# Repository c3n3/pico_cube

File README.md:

# pico_cube
A LED cube from a pico

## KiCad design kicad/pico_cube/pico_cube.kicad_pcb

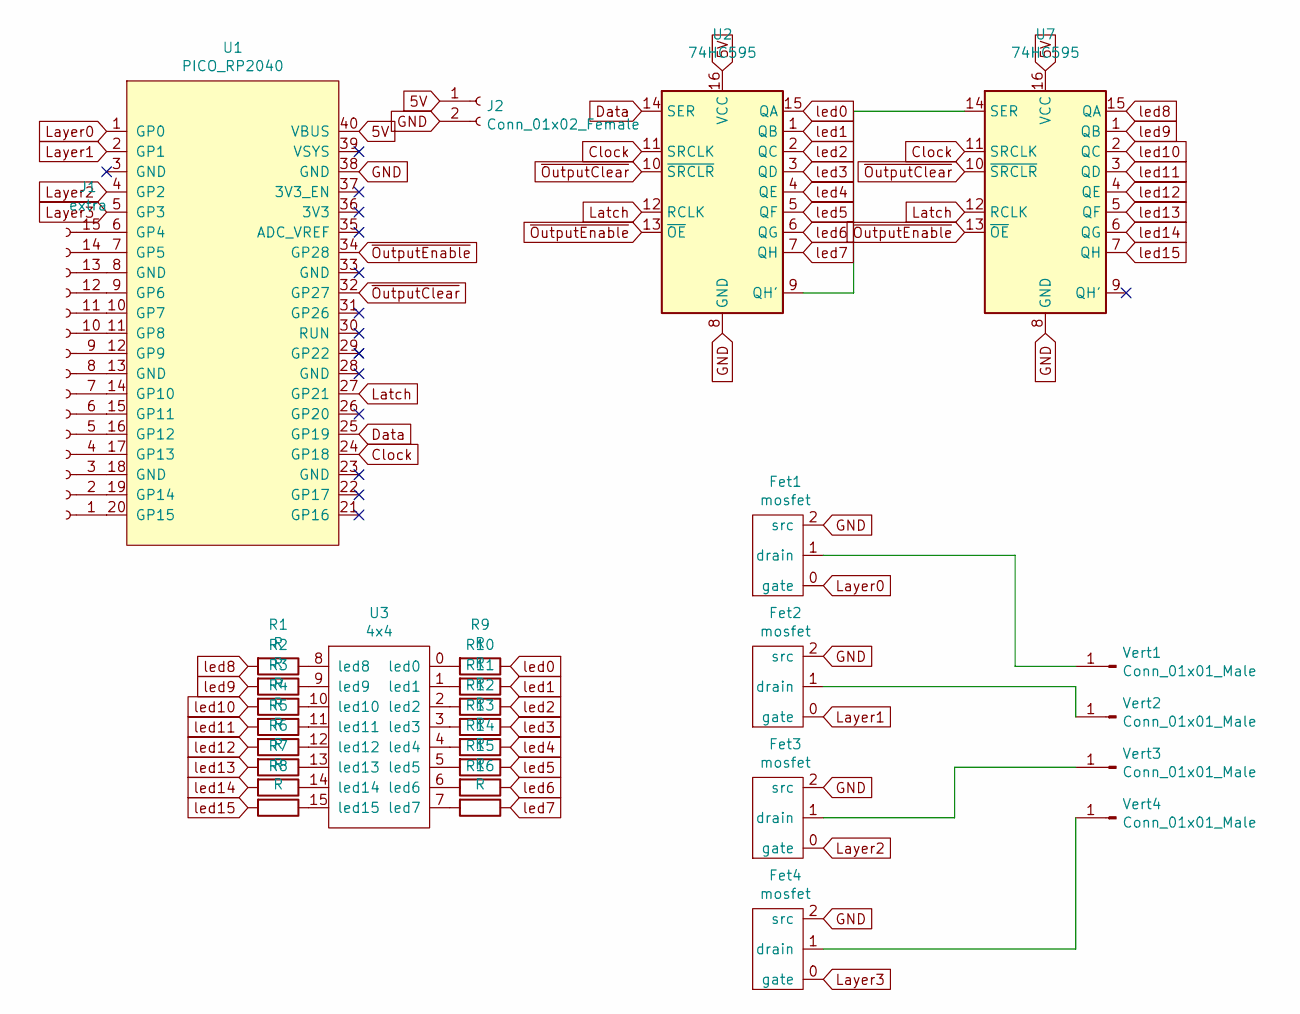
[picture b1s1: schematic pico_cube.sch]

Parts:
Fet1, Fet2, Fet3, Fet4: mosfet
J1: extra; PinHeader_1x15_P2.54mm_Vertical
J2: Conn_01x02_Female; PinHeader_1x02_P2.54mm_Vertical
R1, R2, R3, R4, R5, R6, R7, R8, R9, R10, R11, R12, R13, R14, R15, R16: R; R_Axial_DIN0204_L3.6mm_D1.6mm_P7.62mm_Horizontal
U1: PICO_RP2040; pico
U2, U7: 74HC595; SN74HC595N
U3: 4x4
Vert1, Vert2, Vert3, Vert4: Conn_01x01_Male; pin

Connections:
5V: J2.1, U1.40 (VBUS), U2.16 (VCC), U7.16 (VCC)
Clock: U1.24 (GP18), U2.11 (SRCLK), U7.11 (SRCLK)
Data: U1.25 (GP19), U2.14 (SER)
GND: Fet1.2 (src), Fet2.2 (src), Fet3.2 (src), Fet4.2 (src), J2.2, U1.38 (GND), U2.8 (GND), U7.8 (GND)
Latch: U1.27 (GP21), U2.12 (RCLK), U7.12 (RCLK)
Layer0: Fet1.0 (gate), U1.1 (GP0)
Layer1: Fet2.0 (gate), U1.2 (GP1)
Layer2: Fet3.0 (gate), U1.4 (GP2)
Layer3: Fet4.0 (gate), U1.5 (GP3)
unnamed: Fet1.1 (drain), Vert1.1
unnamed: Fet2.1 (drain), Vert2.1
unnamed: Fet3.1 (drain), Vert3.1
unnamed: Fet4.1 (drain), Vert4.1
unnamed: J1.1, U1.20 (GP15)
unnamed: J1.2, U1.19 (GP14)
unnamed: J1.3, U1.18 (GND)
unnamed: J1.4, U1.17 (GP13)
unnamed: J1.5, U1.16 (GP12)
unnamed: J1.6, U1.15 (GP11)
unnamed: J1.7, U1.14 (GP10)
unnamed: J1.8, U1.13 (GND)
unnamed: J1.9, U1.12 (GP9)
unnamed: J1.10, U1.11 (GP8)
unnamed: J1.11, U1.10 (GP7)
unnamed: J1.12, U1.9 (GP6)
unnamed: J1.13, U1.8 (GND)
unnamed: J1.14, U1.7 (GP5)
unnamed: J1.15, U1.6 (GP4)
unnamed: R1.1, U3.8 (led8)
unnamed: R2.1, U3.9 (led9)
unnamed: R3.1, U3.10 (led10)
unnamed: R4.1, U3.11 (led11)
unnamed: R5.1, U3.12 (led12)
unnamed: R6.1, U3.13 (led13)
unnamed: R7.1, U3.14 (led14)
unnamed: R8.1, U3.15 (led15)
unnamed: R9.2, U3.0 (led0)
unnamed: R10.2, U3.1 (led1)
unnamed: R11.2, U3.2 (led2)
unnamed: R12.2, U3.3 (led3)
unnamed: R13.2, U3.4 (led4)
unnamed: R14.2, U3.5 (led5)
unnamed: R15.2, U3.6 (led6)
unnamed: R16.2, U3.7 (led7)
unnamed: U2.9 (QH'), U7.14 (SER)
led0: R9.1, U2.15 (QA)
led1: R10.1, U2.1 (QB)
led2: R11.1, U2.2 (QC)
led3: R12.1, U2.3 (QD)
led4: R13.1, U2.4 (QE)
led5: R14.1, U2.5 (QF)
led6: R15.1, U2.6 (QG)
led7: R16.1, U2.7 (QH)
led8: R1.2, U7.15 (QA)
led9: R2.2, U7.1 (QB)
led10: R3.2, U7.2 (QC)
led11: R4.2, U7.3 (QD)
led12: R5.2, U7.4 (QE)
led13: R6.2, U7.5 (QF)
led14: R7.2, U7.6 (QG)
led15: R8.2, U7.7 (QH)
~OutputClear: U1.32 (GP27), U2.10 (~SRCLR), U7.10 (~SRCLR)
~OutputEnable: U1.34 (GP28), U2.13 (~OE), U7.13 (~OE)

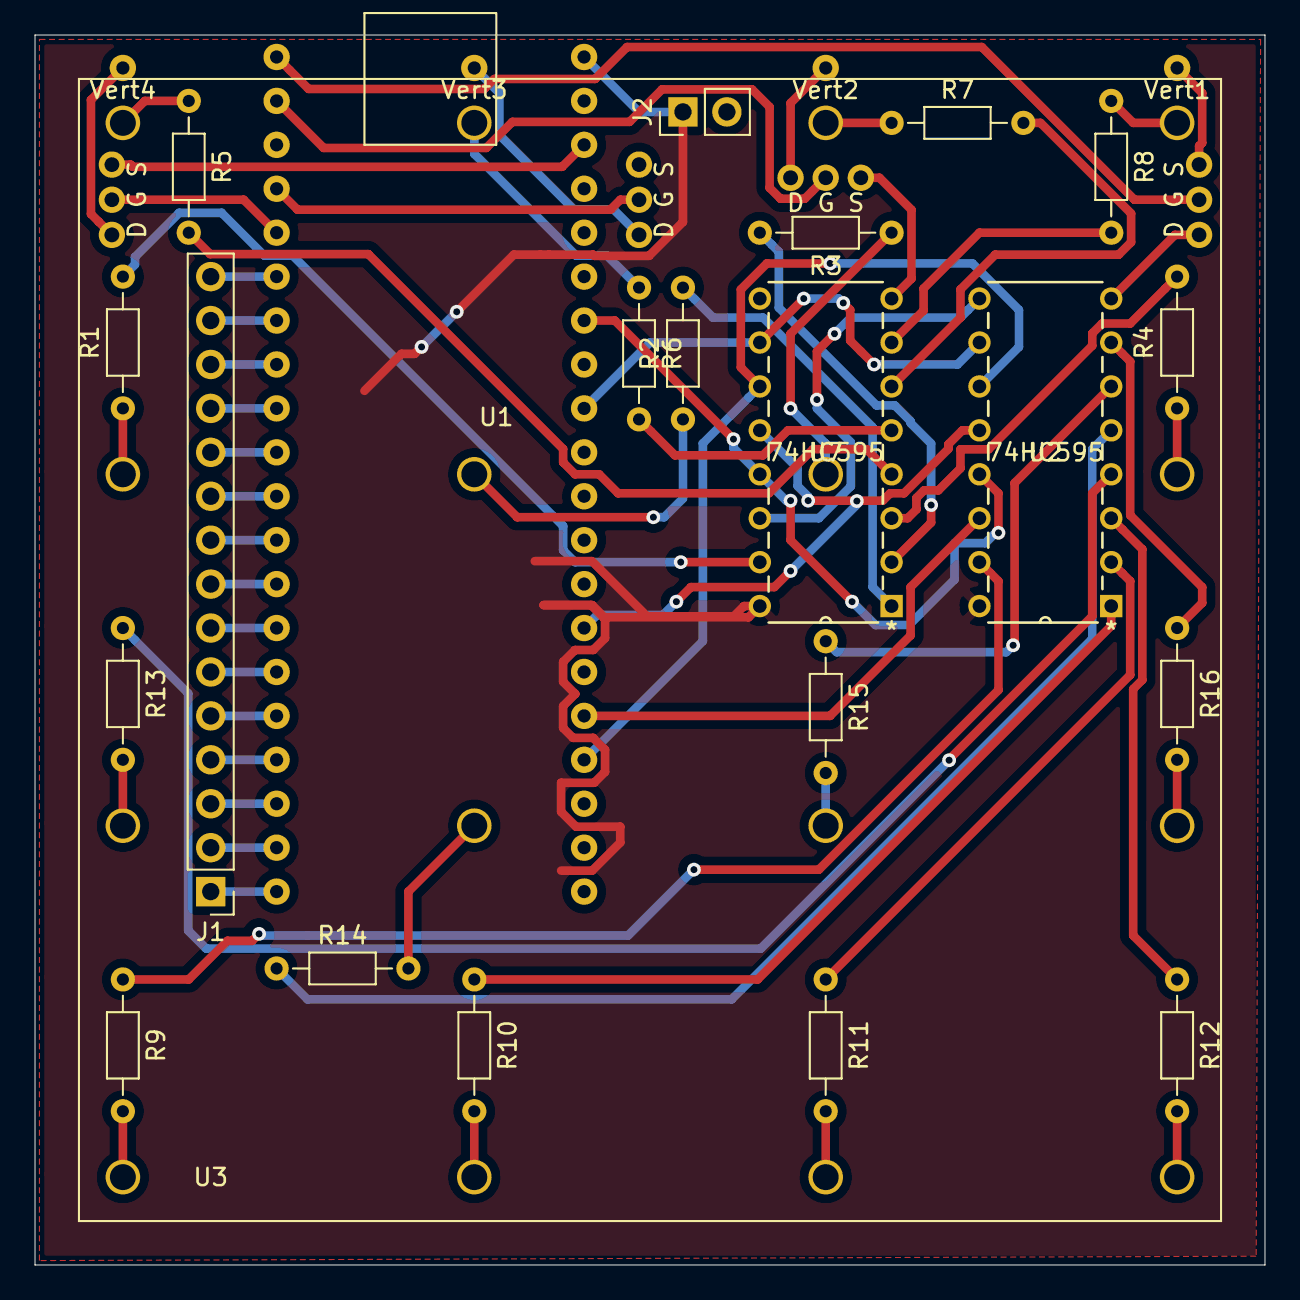
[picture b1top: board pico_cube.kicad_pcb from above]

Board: 2 copper layers, 71.1 x 71.1 mm, 30 parts (0 on the bottom side), 63 nets.

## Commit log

2021-07-28 Add the kicad files for the pico cube
2021-07-28 Made gbr files
2021-08-11 Made the cube work

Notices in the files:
parts and their libraries:
Copyright 2016 Accelerated Designs. All rights reserved.
